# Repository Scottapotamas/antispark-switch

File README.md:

# antispark-switch

High current mosfet based switch for soft-starting capacitive loads.

This is going to be interesting to assemble...

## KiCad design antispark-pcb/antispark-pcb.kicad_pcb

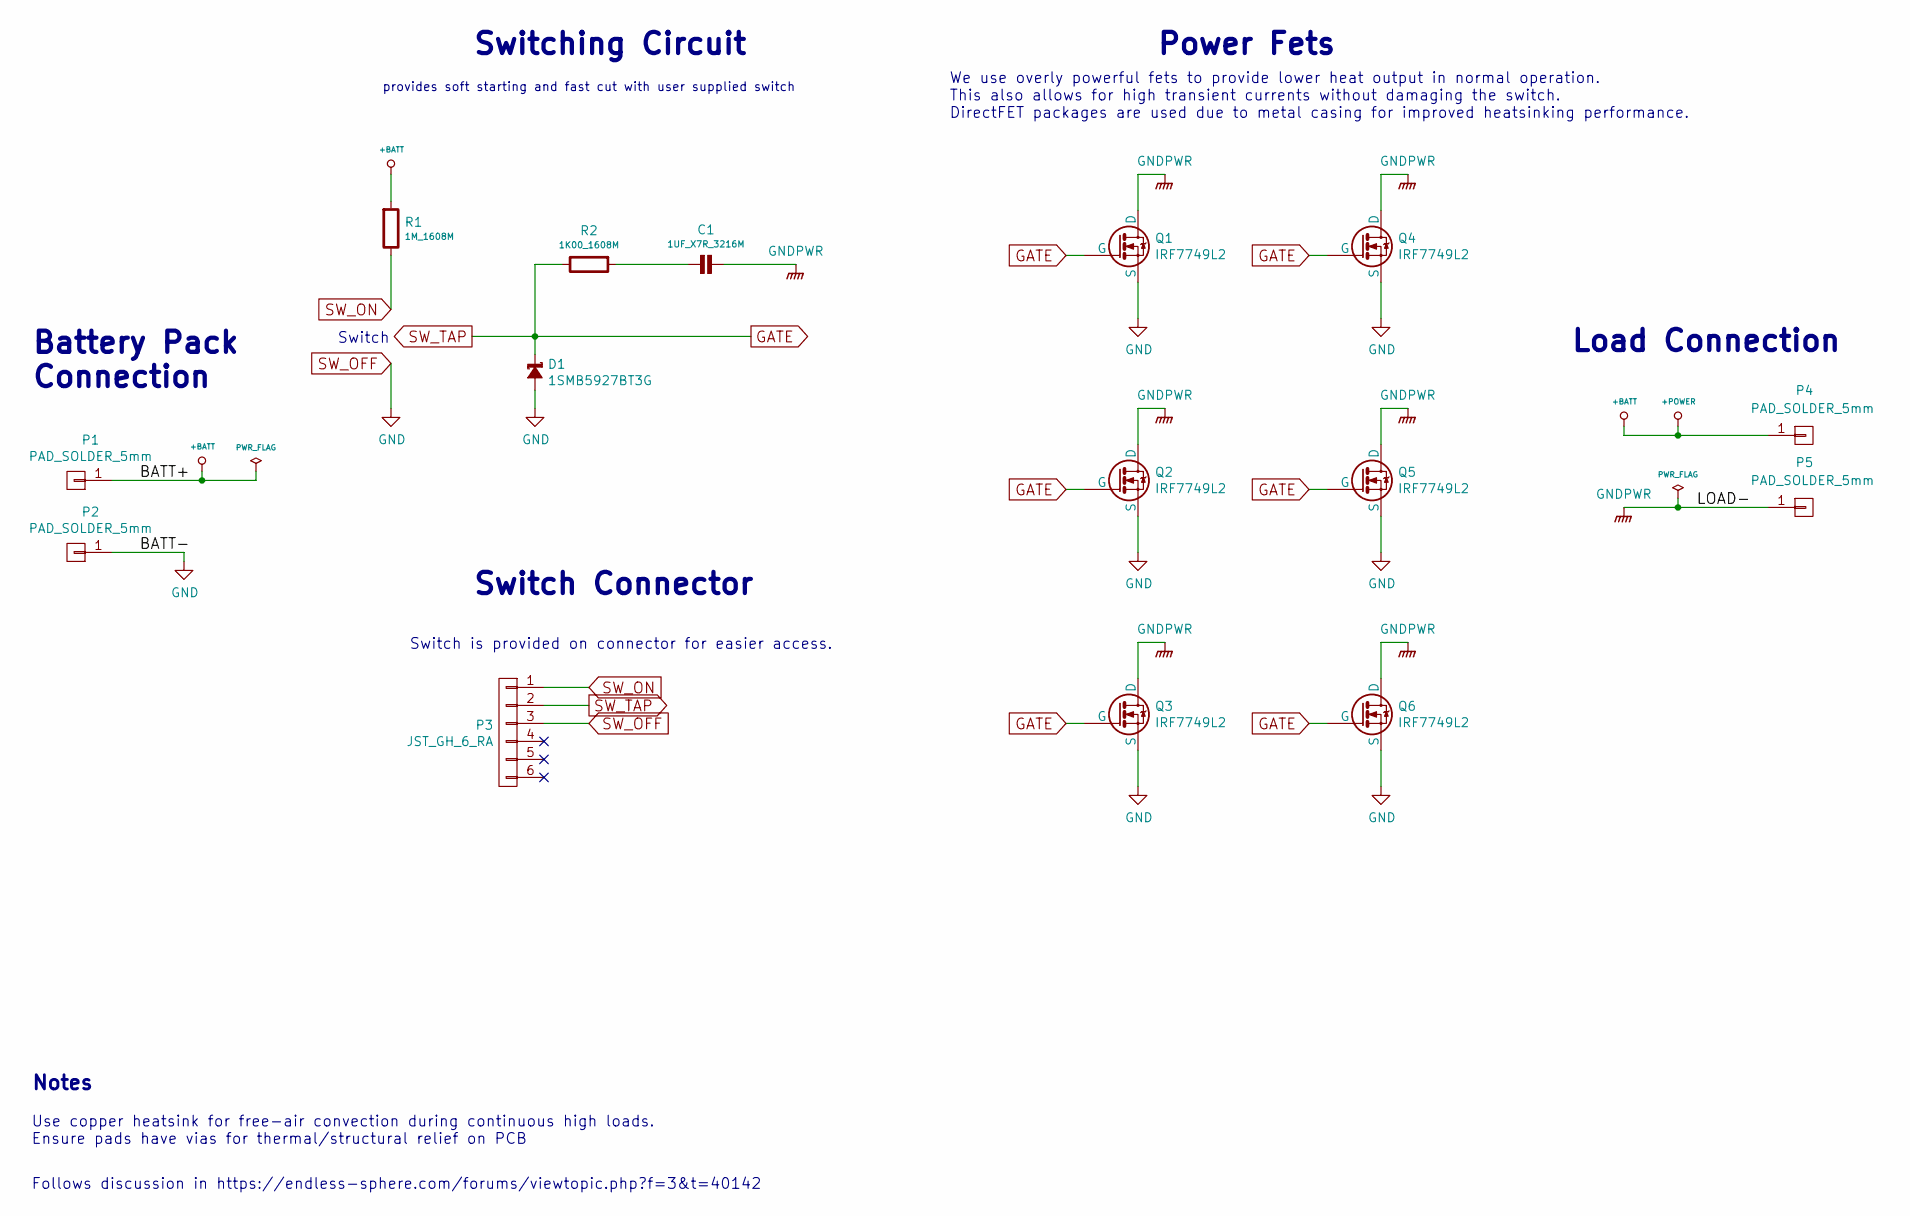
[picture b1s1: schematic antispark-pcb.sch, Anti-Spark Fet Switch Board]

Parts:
C1: 1UF_X7R_3216M; CAPC3216X135N
D1: 1SMB5927BT3G; SODFL5336X245N
P1, P2, P4, P5: PAD_SOLDER_5mm
P3: JST_GH_6_RA; SM06B-GHS-TB
Q1, Q2, Q3, Q4, Q5, Q6: IRF7749L2; directFET_L8
R1: 1M_1608M; RESC1608X50N
R2: 1K00_1608M; RESC1608X50N

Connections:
+BATT: P1.1, P4.1, R1.1
GATE: D1.C, P3.2, Q1.G, Q2.G, Q3.G, Q4.G, Q5.G, Q6.G, R2.2
GNDPWR: C1.1, P5.1, Q1.D, Q2.D, Q3.D, Q4.D, Q5.D, Q6.D
unnamed: C1.2, R2.1
SW_OFF: D1.A, P2.1, P3.3, Q1.S, Q2.S, Q3.S, Q4.S, Q5.S, Q6.S
SW_ON: P3.1, R1.2

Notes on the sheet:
Battery Pack Connection
Load Connection
Switching Circuit
Power Fets
We use overly powerful fets to provide lower heat output in normal operation. This also allows for high transient currents without damaging the switch. DirectFET packages are used due to metal casing for improved heatsinking performance.
Switch
Switch Connector
Switch is provided on connector for easier access.
Follows discussion in https://endless-sphere.com/forums/viewtopic.php?f=3&t=40142
Use copper heatsink for free-air convection during continuous high loads. Ensure pads have vias for thermal/structural relief on PCB
Notes
provides soft starting and fast cut with user supplied switch

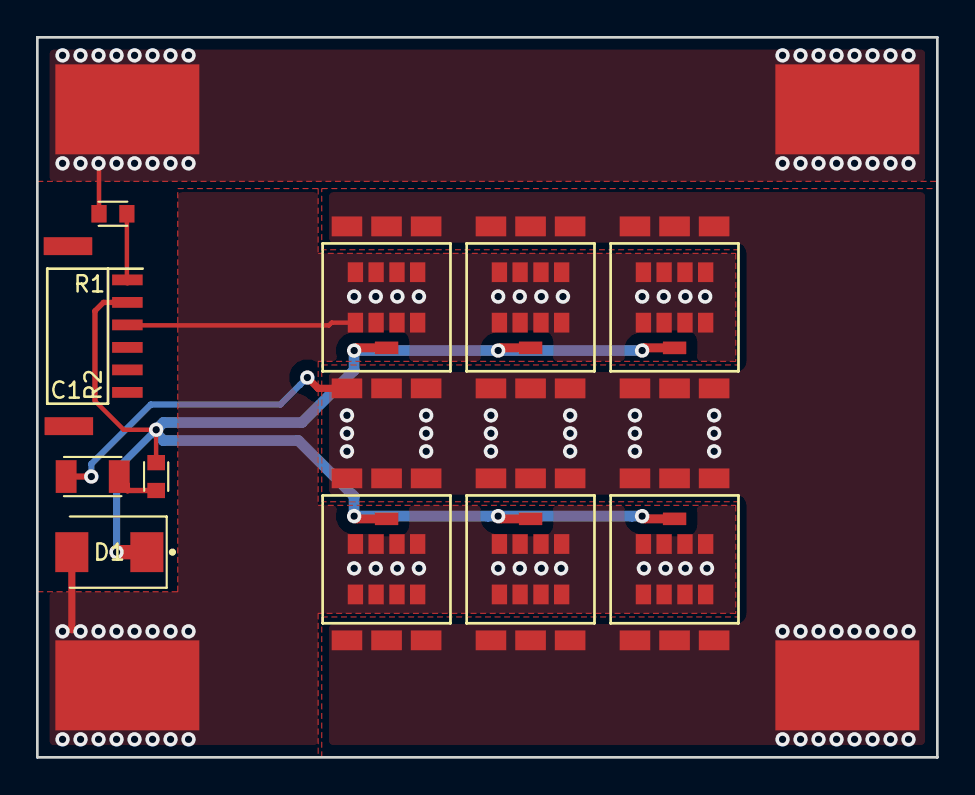
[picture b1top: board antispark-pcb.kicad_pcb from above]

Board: 2 copper layers, 50.0 x 40.0 mm, 15 parts (0 on the bottom side), 6 nets.

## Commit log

2017-09-28 Schematic and PCB roughed out
    Parts, design, layout mostly completed.
    Most cosmetics added.
2017-09-28 Minor tidy and positioning of text
    Cleanup of pours and text locations for cleaner appearance.
2017-09-28 Added renders and pdf of schematic
2017-09-28 Added render to readme
2017-10-06 Added gerber files
2017-10-06 Added BoM
